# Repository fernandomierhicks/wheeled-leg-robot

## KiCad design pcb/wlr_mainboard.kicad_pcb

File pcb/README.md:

# Main board — Teensy 4.1 + ESP32 + CAN + JST-XH I/O

KiCad 10 project `wlr_mainboard` — replaces the hand-wired 90 × 70 mm perfboard
(`components/datasheets/custom board/`).

**Status (2026-10-08): schematic done (ERC 0 errors / 0 warnings), PCB fully
routed — DRC 0 violations, 0 unconnected, 0 schematic parity issues.**

> **Before ordering: double-check every pinout.** Connector pin orders were
> copied from the perfboard cables (photo, sketch and answers). The red note at
> the top of the schematic lists every connector and the specific doubts below.
> If a pin order changes, swap the nets in the schematic, update the PCB (F8)
> and re-route that connector.

## Files

| File | What |
|---|---|
| `wlr_mainboard.kicad_pro` | project; holds the OSH Park design rules and net classes |
| `wlr_mainboard.kicad_sch` | single A2 sheet; every pin goes to a net label or power symbol |
| `wlr_mainboard.kicad_pcb` | 4-layer board, routed, In1 GND / In2 +5V planes filled |
| `lib/wlr.kicad_sym` | Teensy 4.1, ESP32 DevKit V1 30-pin, SN65HVD230 module, power symbols `+3V3_TEENSY`, `+3V3_ESP32`, `VIN_TEENSY` |
| `lib/wlr.pretty/` | matching footprints (socket strips only in the courtyard, so parts can sit under the modules) |
| `sym-lib-table`, `fp-lib-table` | project-local libraries via `${KIPRJMOD}` |

These files are the source of truth: edit them in KiCad as usual and keep the
two in sync with *Tools → Update PCB from Schematic* (F8). They were generated
once by a throw-away script; nothing regenerates them.

## Board

- 90 × 70 mm, 4 × M2 (Ø2.2 NPTH) 2 mm in from the corners — same outline and
  holes as the perfboard (`cad/v5 Ai designed/Box/Electronics/CustomBoard`).
- Teensy USB and ESP32 USB-C at the top edge (they overhang it slightly).
- Teensy 4.1 and ESP32 on female sockets. Low parts sit under them:
  R1–R7, D1, D2, Q1 under the Teensy; U5, C2, R8–R12 under the ESP32. Seat
  them flat (keep under ~7 mm).
- CAN modules (U3 AK45 bus, U4 ODrive bus) stand on their 6-pin edge header,
  as on the perfboard; footprint assumes the module body on the +x side.
- Every JST-XH header has its latch side toward the board centre, like the
  perfboard, so the existing cables plug in the same way.
- Back silkscreen prints the pin name next to every connector pad.
- No copper pour or vias under the ESP32 antenna (rule area).
- Fully through-hole.

### OSH Park 4-layer

| Item | Value |
|---|---|
| Stackup | 1 oz / 7.87 mil prepreg / 0.5 oz / 39 mil core / 0.5 oz / 7.87 mil prepreg / 1 oz, FR408-HR (εr 3.61), ENIG, 1.6 mm nominal |
| Layers | L1 signal · L2 **GND plane** · L3 **+5V plane** · L4 signal |
| Rules (Board Setup) | 0.127 mm track / clearance, 0.254 mm drill, 0.102 mm annular ring, 0.381 mm copper-to-edge, 0.254 mm hole-to-copper |
| Net classes | Default 0.2 mm · Power 0.5 mm (`GND`, `+5V`, `VIN_TEENSY`, `+3V3_*`) · CAN 0.3 mm (`CAN?_H/L`) |
| Price | 90 × 70 mm ≈ 9.8 in² ≈ $98 for 3 boards ($10/in²) |

### Routing

Autorouted with Freerouting 2.5.0 (Specctra DSN → SES), then checked in KiCad.

- Signals on L1/L4 only; every GND and +5V pin connects straight to its plane
  through thermal reliefs (no GND/+5V traces).
- Widths: signals 0.2 mm, CAN pairs 0.3 mm, `+3V3_TEENSY` / `+3V3_ESP32` /
  `VIN_TEENSY` 0.5 mm. 17 vias (0.6 / 0.3 mm), ~2.6 m of track.
- No vias or pours in the ESP32 antenna area.
- To re-route with Freerouting: *File → Export → Specctra DSN*, shrink the DSN
  `boundary` ~0.25 mm (Freerouting ignores KiCad's 0.381 mm edge clearance),
  run with `--router.automatic_neckdown=false` (neckdown makes sub-0.127 mm
  traces), then *File → Import → Specctra Session*, refill zones (B), run DRC.
  Export the DSN from the board inside this folder, next to the `.kicad_pro`,
  or the net classes (power/CAN widths) are lost.

## Power

- `+5V` from J10 (buck output) feeds ESP32 VIN, the NeoPixel strip, IMU, ELRS
  receiver, buzzer and U5.
- Teensy VIN through **D1 (1N5817)**: Teensy USB can no longer back-feed the
  5 V rail, so the VUSB–VIN pad can stay uncut. The ESP32 DevKit still
  back-feeds `+5V` from its USB-C through its own diode (as on the perfboard).
- Two 3.3 V rails, never tied: `+3V3_TEENSY` (Teensy regulator) → CAN modules,
  UART6/7, I2C, spare header; `+3V3_ESP32` (DevKit regulator) → TFT, lasers,
  laser INT pull-ups, ESP32 spare header.

## Connectors

Orders are as seen on the board from the top (USB at the top). TX/RX are named
from the MCU (Teensy) side.

| Ref | Name | Footprint | Physical order on the board | Nets (pin 1 first) |
|---|---|---|---|---|
| J1 | BUZZER | XH 2p | top edge, left→right: BZ-, BZ+ | BUZZER_LOW, +5V |
| J2 | RGB_LED | XH 4p | left edge, top→bottom: B, G, GND, R | LED_R, GND, LED_G, LED_B |
| J3 | ELRS_RX | XH 4p | left edge, top→bottom: GND, 5V, RX (→Teensy 16), TX (Teensy 17→) | RC_TX, RC_RX_IN, +5V, GND |
| J4 | IMU_SIG | XH 6p | left edge, top→bottom: RST, INT, CS, AD0, SDA, SCL | IMU_SCK, IMU_MISO, IMU_MOSI, IMU_CS, IMU_INT, IMU_RST |
| J5 | IMU_PWR | XH 2p | left edge, top→bottom: GND, VCC (+5V) | +5V, GND |
| J6 | AK45_UART2 | XH 3p | bottom, inner row, left→right: GND, TX (Teensy 14), RX (Teensy 15) | AK2_RX, AK2_TX, GND |
| J7 | AK45_UART1 | XH 3p | bottom, outer row, left→right: GND, TX (Teensy 8), RX (Teensy 7) | AK1_RX, AK1_TX, GND |
| J8 | AK45_CAN | XH 2p | bottom, left→right: CANH, CANL | CAN2_L, CAN2_H |
| J9 | ODRIVE_CAN | XH 3p | bottom, left→right: GND, CANH, CANL | CAN3_L, CAN3_H, GND |
| J10 | 5V_IN | XH 2p | bottom, left→right: GND, +5V | +5V, GND |
| J11–J14 | LASER1–4 | XH 6p | bottom (1/2 outer row, 3/4 inner row), left→right: XSHUT, INT, SDA, SCL, GND, 3V3 | +3V3_ESP32, GND, TOF_SCL, TOF_SDA, LASERn_INT, LASERn_XSHUT |
| J15 | TFT_PWR | XH 2p | right edge, top→bottom: GND, 3V3 | GND, +3V3_ESP32 |
| J16 | TFT_SIG | XH 6p | right edge, top→bottom: SCL, SDA, RST, DC, CS, BL | TFT_SCK, TFT_MOSI, TFT_RST, TFT_DC, TFT_CS, TFT_BL |
| J17 | NEOPIXEL | XH 3p | right edge, top→bottom: 5V, GND, DATA | +5V, GND, NEO_DATA |
| J18 | LIMIT_L | XH 2p | *new*, right edge, top→bottom: GND, SIG (Teensy 23) | GND, LIMIT_L |
| J19 | LIMIT_R | XH 2p | *new*, right edge, top→bottom: GND, SIG (Teensy 22) | GND, LIMIT_R |
| J20 | UART6 | XH 4p | *new*, inner column, top→bottom: TX (24), RX (25), 3V3, GND | GND, +3V3_TEENSY, UART6_RX, UART6_TX |
| J21 | UART7 | XH 4p | *new*, inner column, top→bottom: RX (28), TX (29), 3V3, GND | GND, +3V3_TEENSY, UART7_TX, UART7_RX |
| J22 | I2C | XH 4p | *new*, inner column, top→bottom: SCL (19), SDA (18), 3V3, GND | GND, +3V3_TEENSY, I2C_SDA, I2C_SCL |
| J23 | TEENSY_GPIO | 1×14 header | *new*, top→bottom: 3V3, 26, 27, 32, GND, 41…33 — pins GND…33 sit level with the matching Teensy pins | — |
| J24 | ESP32_GPIO | 1×5 header | *new*, top→bottom: GND, 3V3, IO19, IO32, IO33 | — |

Lasers 1–4 = firmware sensors 0–3: XSHUT on ESP32 GPIO14/27/26/25, INT on
GPIO34/35/36/39 (10 kΩ pull-ups R9–R12; firmware still polls).

## Open checks before ordering

1. **IMU VCC = +5V** (as told): the BNO08x module must have its own 3.3 V regulator.
2. **IMU MOSI/MISO**: module `SDA` → Teensy 12 (MISO), `AD0` → Teensy 11 (MOSI),
   `SCL` → 13, per the BNO08x datasheet (H_SDA/H_MISO, SA0/H_MOSI).
   `firmware/robot_teensy/pinout.MD` lists SDA/AD0 the other way round —
   verify on the working perfboard.
3. **ELRS RX/TX** naming (J3) assumed from the Teensy side, like the AK45 UARTs.
4. **CAN termination**: the board is one end of each bus — check whether the
   HiLetgo module has a 120 Ω resistor fitted.
5. Confirm the CAN module stands with its body toward the Teensy (+x).
6. Not routed to the module: the IMU `PS0/WAKE` pin (`lib/IMU/README.md` asks
   for it on a future board, but the module only brings it out on solder
   bridges). A spare pin on J23 plus a flying wire would do.

## Parts

Through-hole only.

| Qty | Refs | Part |
|---|---|---|
| 1 | U1 | Teensy 4.1 + 2 × 1×24 female socket (2.54 mm) |
| 1 | U2 | ESP32 DevKit V1 30-pin USB-C + 2 × 1×15 female socket |
| 2 | U3, U4 | HiLetgo SN65HVD230 CAN board |
| 1 | U5 | 74AHCT125 (DIP-14, solder directly — no socket, it sits under the ESP32) |
| 1 | D1 | 1N5817 |
| 1 | D2 | 1N4148 |
| 1 | Q1 | 2N3904 (TO-92) |
| 3 | R1–R3 | 33 Ω (LED) |
| 2 | R4, R5 | 1 kΩ (buzzer base, ELRS RX series) |
| 2 | R6, R7 | 4.7 kΩ (I2C pull-ups) |
| 1 | R8 | 330 Ω (NeoPixel data) |
| 4 | R9–R12 | 10 kΩ (laser INT pull-ups) |
| 1 | C1 | 100 µF 10 V radial, Ø6.3 mm, 2.5 mm pitch |
| 1 | C2 | 100 nF disc, 5 mm pitch |
| 7 | J1, J5, J8, J10, J15, J18, J19 | JST B2B-XH-A |
| 4 | J6, J7, J9, J17 | JST B3B-XH-A |
| 5 | J2, J3, J20, J21, J22 | JST B4B-XH-A |
| 6 | J4, J11–J14, J16 | JST B6B-XH-A |
| 1 | J23 | 1×14 male header 2.54 mm |
| 1 | J24 | 1×5 male header 2.54 mm |

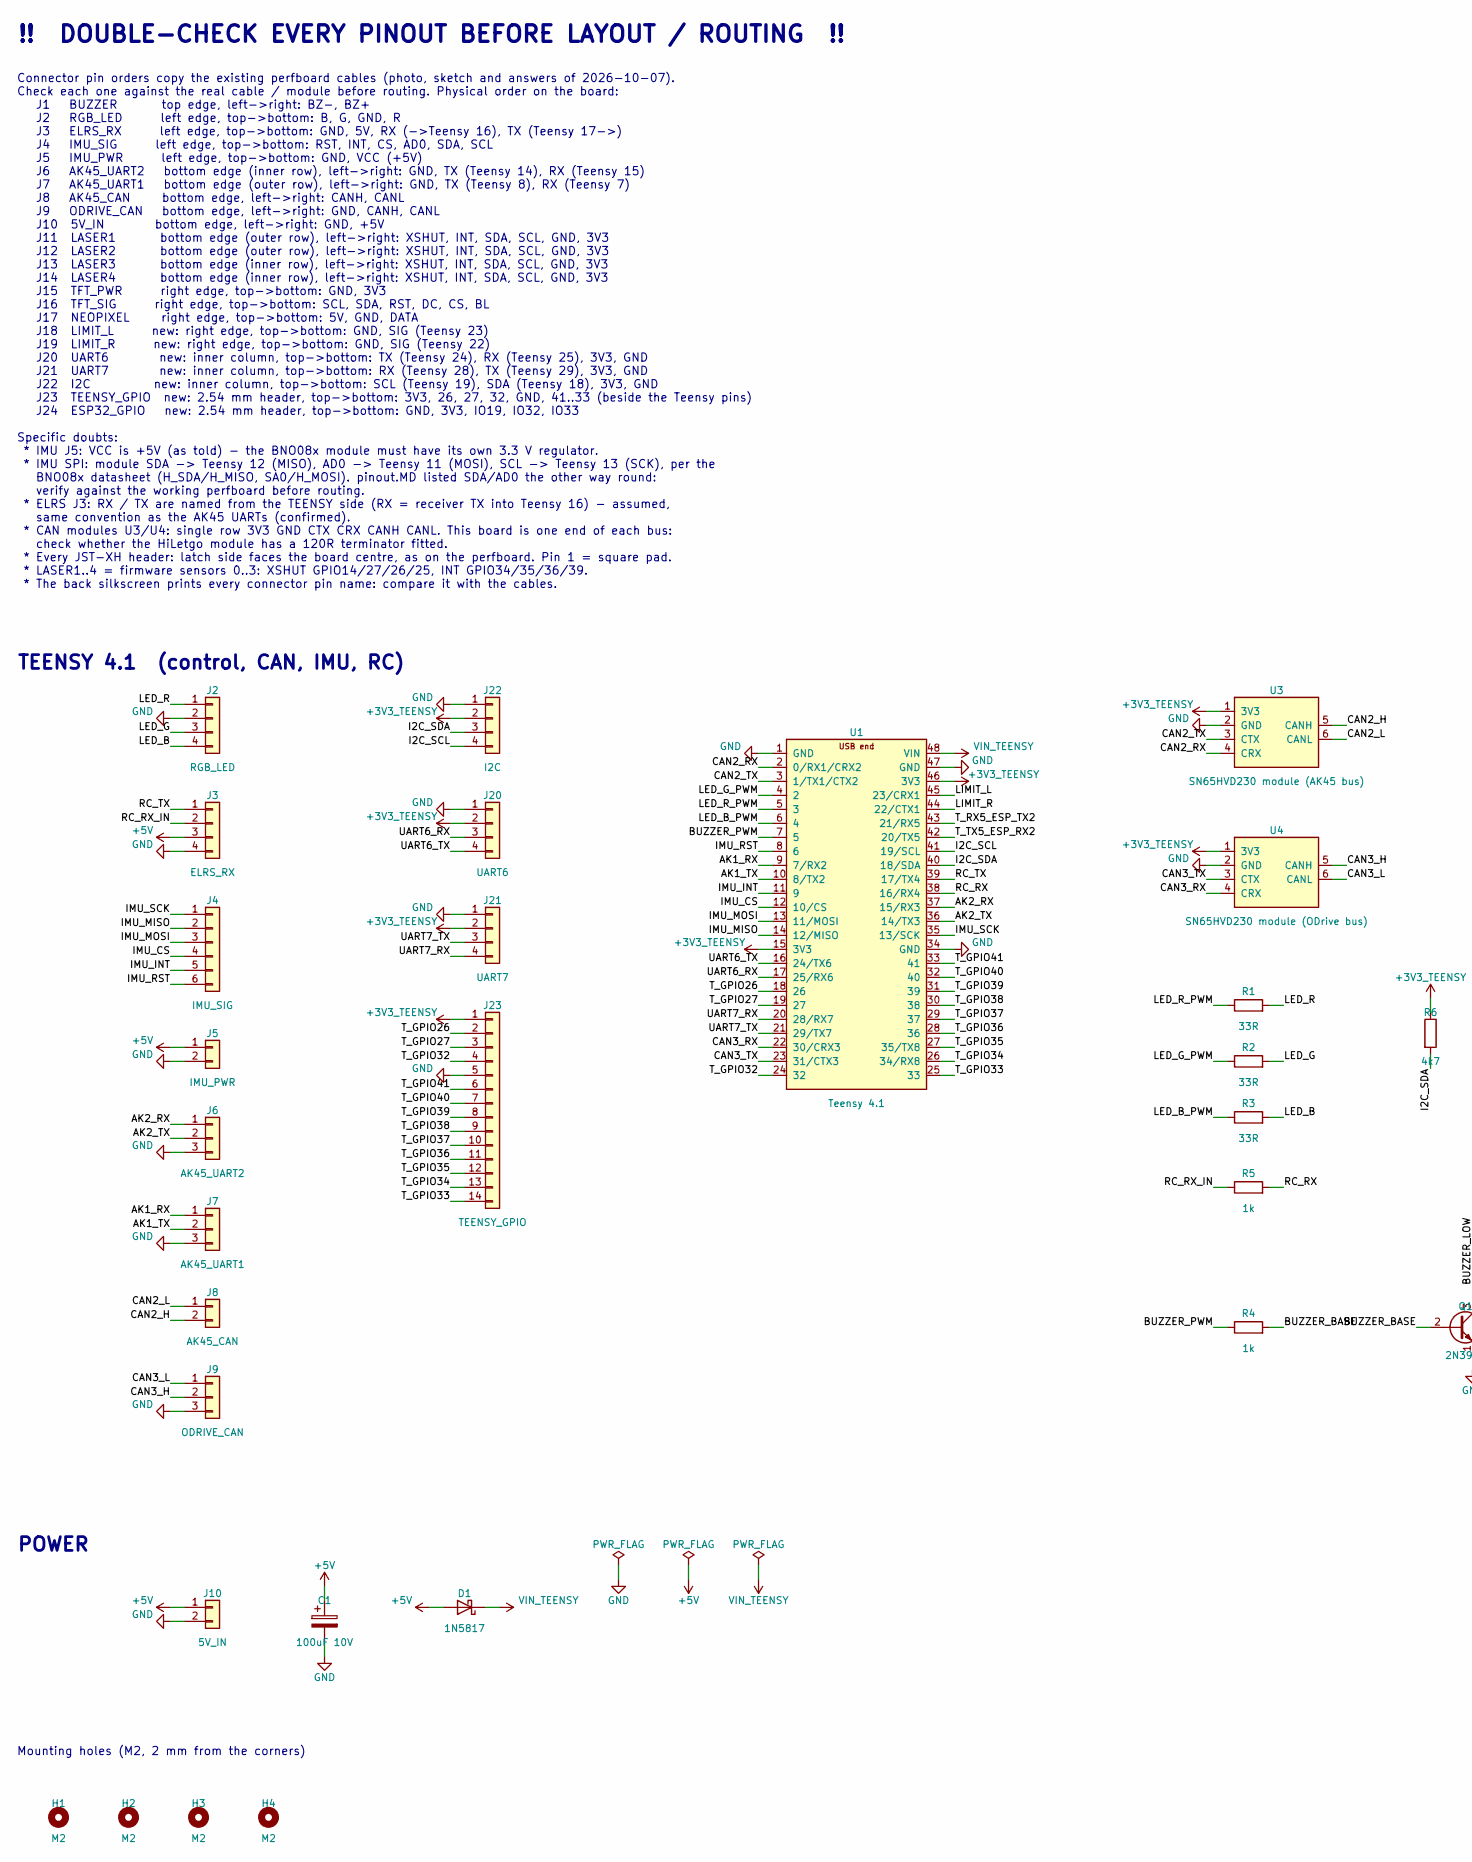
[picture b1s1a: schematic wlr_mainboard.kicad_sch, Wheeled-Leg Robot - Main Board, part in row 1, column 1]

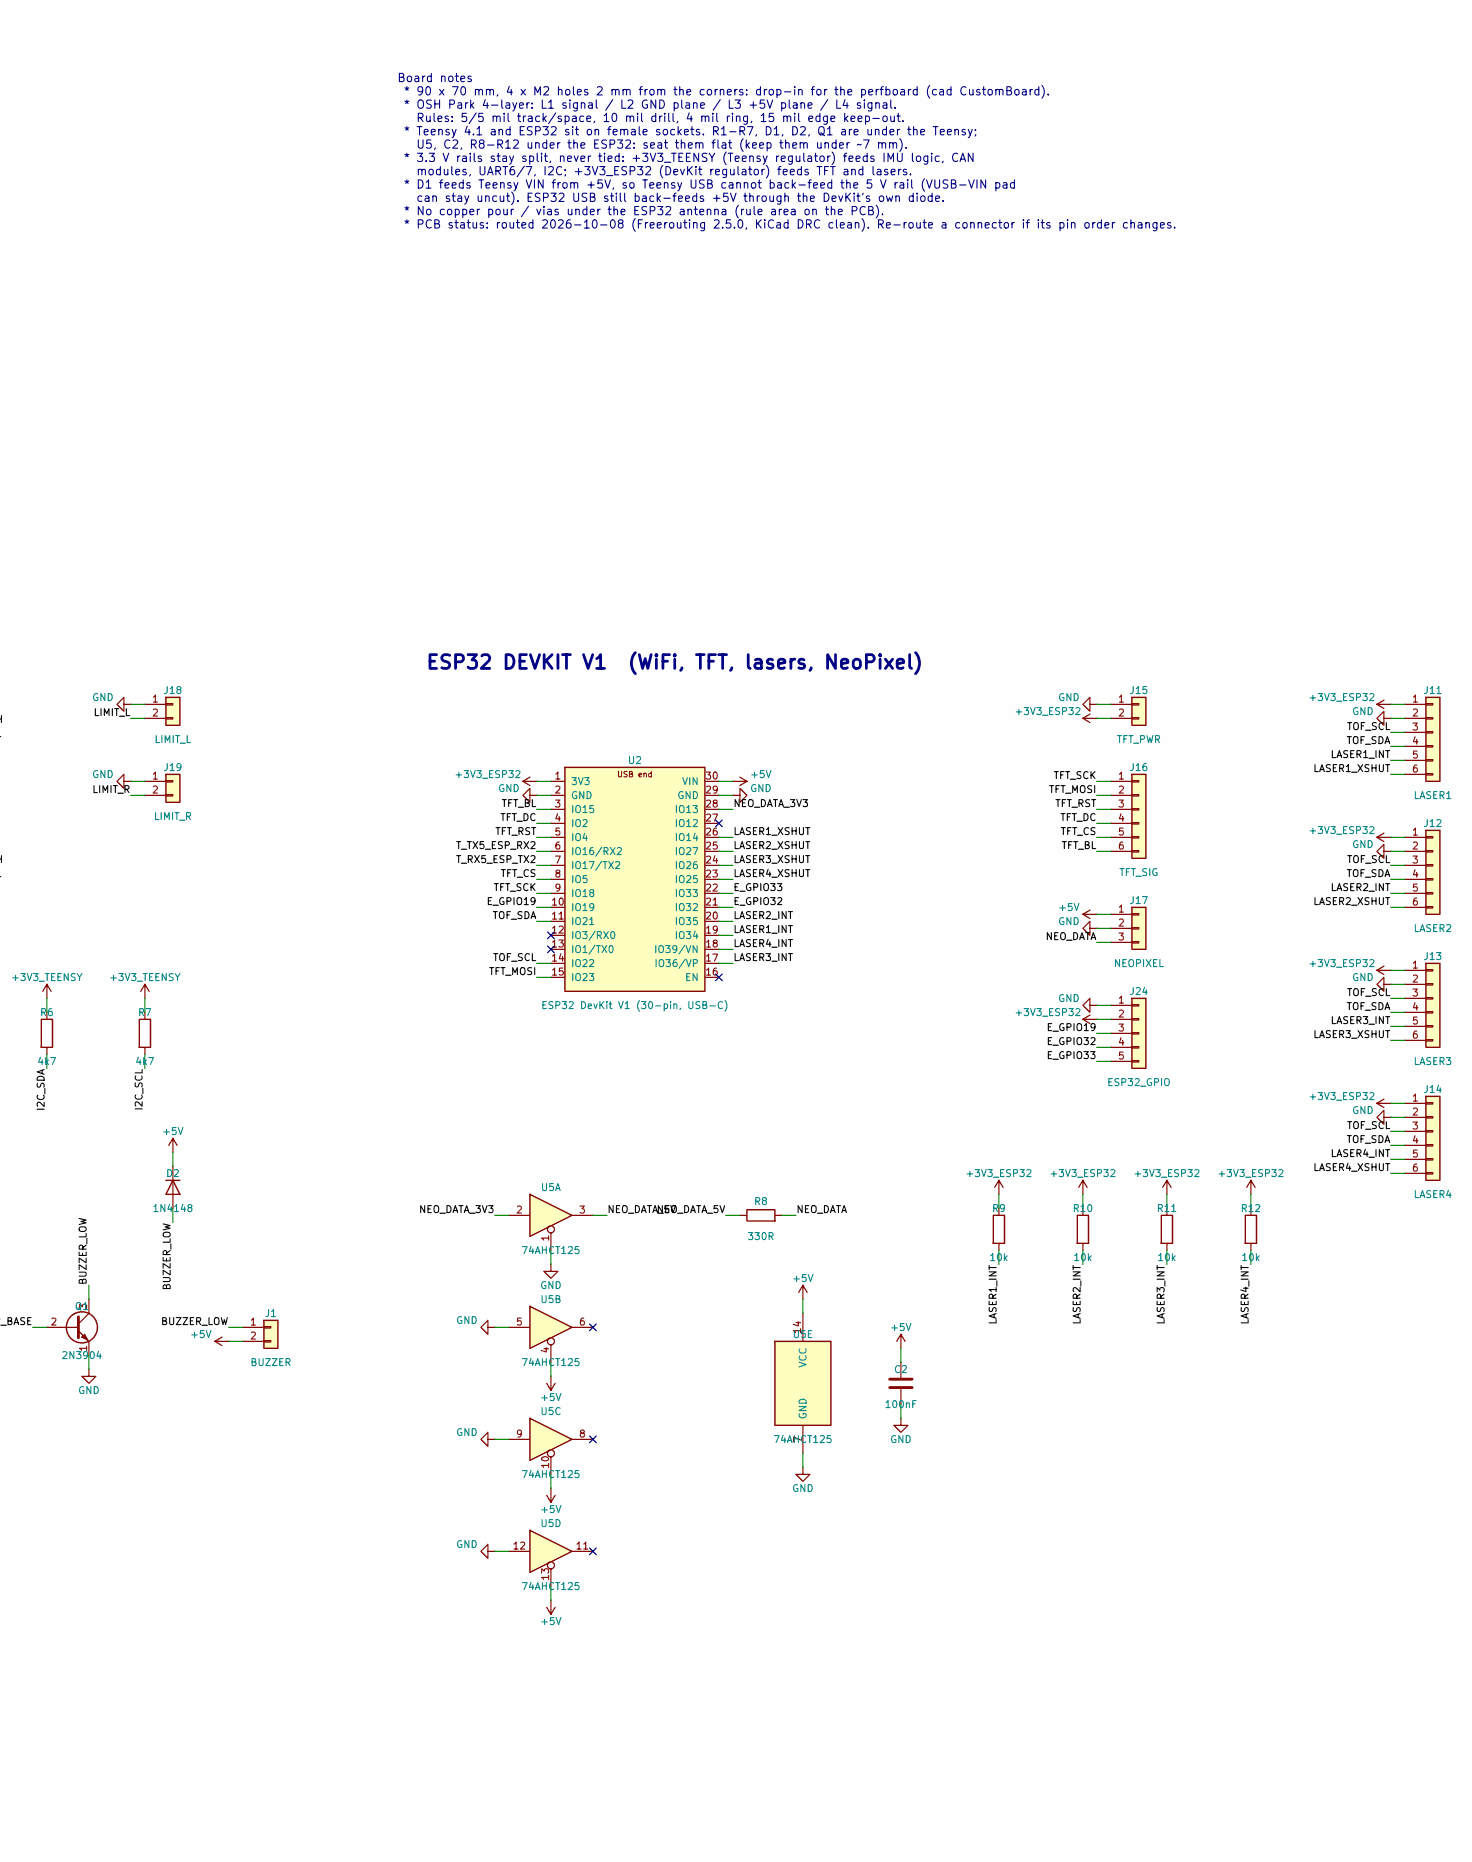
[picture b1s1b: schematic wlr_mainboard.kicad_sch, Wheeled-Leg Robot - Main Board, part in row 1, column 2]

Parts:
C1: 100uF 10V; CP_Radial_D6.3mm_P2.50mm
C2: 100nF; C_Disc_D5.0mm_W2.5mm_P5.00mm
D1: 1N5817; D_DO-41_SOD81_P7.62mm_Horizontal
D2: 1N4148; D_DO-35_SOD27_P7.62mm_Horizontal
H1, H2, H3, H4: M2; MountingHole_2.2mm_M2
J1: BUZZER; JST_XH_B2B-XH-A_1x02_P2.50mm_Vertical
J2: RGB_LED; JST_XH_B4B-XH-A_1x04_P2.50mm_Vertical
J3: ELRS_RX; JST_XH_B4B-XH-A_1x04_P2.50mm_Vertical
J4: IMU_SIG; JST_XH_B6B-XH-A_1x06_P2.50mm_Vertical
J5: IMU_PWR; JST_XH_B2B-XH-A_1x02_P2.50mm_Vertical
J6: AK45_UART2; JST_XH_B3B-XH-A_1x03_P2.50mm_Vertical
J7: AK45_UART1; JST_XH_B3B-XH-A_1x03_P2.50mm_Vertical
J8: AK45_CAN; JST_XH_B2B-XH-A_1x02_P2.50mm_Vertical
J9: ODRIVE_CAN; JST_XH_B3B-XH-A_1x03_P2.50mm_Vertical
J10: 5V_IN; JST_XH_B2B-XH-A_1x02_P2.50mm_Vertical
J11: LASER1; JST_XH_B6B-XH-A_1x06_P2.50mm_Vertical
J12: LASER2; JST_XH_B6B-XH-A_1x06_P2.50mm_Vertical
J13: LASER3; JST_XH_B6B-XH-A_1x06_P2.50mm_Vertical
J14: LASER4; JST_XH_B6B-XH-A_1x06_P2.50mm_Vertical
J15: TFT_PWR; JST_XH_B2B-XH-A_1x02_P2.50mm_Vertical
J16: TFT_SIG; JST_XH_B6B-XH-A_1x06_P2.50mm_Vertical
J17: NEOPIXEL; JST_XH_B3B-XH-A_1x03_P2.50mm_Vertical
J18: LIMIT_L; JST_XH_B2B-XH-A_1x02_P2.50mm_Vertical
J19: LIMIT_R; JST_XH_B2B-XH-A_1x02_P2.50mm_Vertical
J20: UART6; JST_XH_B4B-XH-A_1x04_P2.50mm_Vertical
J21: UART7; JST_XH_B4B-XH-A_1x04_P2.50mm_Vertical
J22: I2C; JST_XH_B4B-XH-A_1x04_P2.50mm_Vertical
J23: TEENSY_GPIO; PinHeader_1x14_P2.54mm_Vertical
J24: ESP32_GPIO; PinHeader_1x05_P2.54mm_Vertical
Q1: 2N3904; TO-92_Inline
R1, R2, R3: 33R; R_Axial_DIN0207_L6.3mm_D2.5mm_P7.62mm_Horizontal
R4, R5: 1k; R_Axial_DIN0207_L6.3mm_D2.5mm_P7.62mm_Horizontal
R6, R7: 4k7; R_Axial_DIN0207_L6.3mm_D2.5mm_P7.62mm_Horizontal
R8: 330R; R_Axial_DIN0207_L6.3mm_D2.5mm_P7.62mm_Horizontal
R9, R10, R11, R12: 10k; R_Axial_DIN0207_L6.3mm_D2.5mm_P7.62mm_Horizontal
U1: Teensy 4.1; Teensy_4.1_Socket
U2: ESP32 DevKit V1 (30-pin, USB-C); ESP32_DevKit_V1_30P_Socket
U3: SN65HVD230 module (AK45 bus); SN65HVD230_Module_Standing
U4: SN65HVD230 module (ODrive bus); SN65HVD230_Module_Standing
U5: 74AHCT125; DIP-14_W7.62mm

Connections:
+3V3_ESP32: J11.1, J12.1, J13.1, J14.1, J15.2, J24.2, R9.1, R10.1, R11.1, R12.1, U2.1 (3V3)
+3V3_TEENSY: J20.2, J21.2, J22.2, J23.1, R6.1, R7.1, U1.15 (3V3), U1.46 (3V3), U3.1 (3V3), U4.1 (3V3)
+5V: C1.1, C2.1, D1.2 (A), D2.1 (K), J1.2, J3.3, J5.1, J10.1, J17.1, U2.30 (VIN), U5.4, U5.10, U5.13, U5.14 (VCC)
/AK1_RX: J7.1, U1.9 (7/RX2)
/AK1_TX: J7.2, U1.10 (8/TX2)
/AK2_RX: J6.1, U1.37 (15/RX3)
/AK2_TX: J6.2, U1.36 (14/TX3)
/BUZZER_BASE: Q1.2 (B), R4.2
/BUZZER_LOW: D2.2 (A), J1.1, Q1.3 (C)
/BUZZER_PWM: R4.1, U1.7 (5)
/CAN2_H: J8.2, U3.5 (CANH)
/CAN2_L: J8.1, U3.6 (CANL)
/CAN2_RX: U1.2 (0/RX1/CRX2), U3.4 (CRX)
/CAN2_TX: U1.3 (1/TX1/CTX2), U3.3 (CTX)
/CAN3_H: J9.2, U4.5 (CANH)
/CAN3_L: J9.1, U4.6 (CANL)
/CAN3_RX: U1.22 (30/CRX3), U4.4 (CRX)
/CAN3_TX: U1.23 (31/CTX3), U4.3 (CTX)
/E_GPIO19: J24.3, U2.10 (IO19)
/E_GPIO32: J24.4, U2.21 (IO32)
/E_GPIO33: J24.5, U2.22 (IO33)
/I2C_SCL: J22.4, R7.2, U1.41 (19/SCL)
/I2C_SDA: J22.3, R6.2, U1.40 (18/SDA)
/IMU_CS: J4.4, U1.12 (10/CS)
/IMU_INT: J4.5, U1.11 (9)
/IMU_MISO: J4.2, U1.14 (12/MISO)
/IMU_MOSI: J4.3, U1.13 (11/MOSI)
/IMU_RST: J4.6, U1.8 (6)
/IMU_SCK: J4.1, U1.35 (13/SCK)
/LASER1_INT: J11.5, R9.2, U2.19 (IO34)
/LASER1_XSHUT: J11.6, U2.26 (IO14)
/LASER2_INT: J12.5, R10.2, U2.20 (IO35)
/LASER2_XSHUT: J12.6, U2.25 (IO27)
/LASER3_INT: J13.5, R11.2, U2.17 (IO36/VP)
/LASER3_XSHUT: J13.6, U2.24 (IO26)
/LASER4_INT: J14.5, R12.2, U2.18 (IO39/VN)
/LASER4_XSHUT: J14.6, U2.23 (IO25)
/LED_B: J2.4, R3.2
/LED_B_PWM: R3.1, U1.6 (4)
/LED_G: J2.3, R2.2
/LED_G_PWM: R2.1, U1.4 (2)
/LED_R: J2.1, R1.2
/LED_R_PWM: R1.1, U1.5 (3)
/LIMIT_L: J18.2, U1.45 (23/CRX1)
/LIMIT_R: J19.2, U1.44 (22/CTX1)
/NEO_DATA: J17.3, R8.2
/NEO_DATA_3V3: U2.28 (IO13), U5.2
/NEO_DATA_5V: R8.1, U5.3
/RC_RX: R5.2, U1.38 (16/RX4)
/RC_RX_IN: J3.2, R5.1
/RC_TX: J3.1, U1.39 (17/TX4)
/TFT_BL: J16.6, U2.3 (IO15)
/TFT_CS: J16.5, U2.8 (IO5)
/TFT_DC: J16.4, U2.4 (IO2)
/TFT_MOSI: J16.2, U2.15 (IO23)
/TFT_RST: J16.3, U2.5 (IO4)
/TFT_SCK: J16.1, U2.9 (IO18)
/TOF_SCL: J11.3, J12.3, J13.3, J14.3, U2.14 (IO22)
/TOF_SDA: J11.4, J12.4, J13.4, J14.4, U2.11 (IO21)
/T_GPIO26: J23.2, U1.18 (26)
/T_GPIO27: J23.3, U1.19 (27)
/T_GPIO32: J23.4, U1.24 (32)
/T_GPIO33: J23.14, U1.25 (33)
/T_GPIO34: J23.13, U1.26 (34/RX8)
/T_GPIO35: J23.12, U1.27 (35/TX8)
/T_GPIO36: J23.11, U1.28 (36)
/T_GPIO37: J23.10, U1.29 (37)
/T_GPIO38: J23.9, U1.30 (38)
/T_GPIO39: J23.8, U1.31 (39)
/T_GPIO40: J23.7, U1.32 (40)
/T_GPIO41: J23.6, U1.33 (41)
/T_RX5_ESP_TX2: U1.43 (21/RX5), U2.7 (IO17/TX2)
/T_TX5_ESP_RX2: U1.42 (20/TX5), U2.6 (IO16/RX2)
/UART6_RX: J20.3, U1.17 (25/RX6)
/UART6_TX: J20.4, U1.16 (24/TX6)
/UART7_RX: J21.4, U1.20 (28/RX7)
/UART7_TX: J21.3, U1.21 (29/TX7)
GND: C1.2, C2.2, J2.2, J3.4, J5.2, J6.3, J7.3, J9.3, J10.2, J11.2, J12.2, J13.2, J14.2, J15.1, J17.2, J18.1, J19.1, J20.1, J21.1, J22.1, J23.5, J24.1, Q1.1 (E), U1.1 (GND), U1.34 (GND), U1.47 (GND), U2.2 (GND), U2.29 (GND), U3.2 (GND), U4.2 (GND), U5.1, U5.5, U5.7 (GND), U5.9, U5.12
VIN_TEENSY: D1.1 (K), U1.48 (VIN)

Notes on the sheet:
!! DOUBLE-CHECK EVERY PINOUT BEFORE LAYOUT / ROUTING !!
Board notes * 90 x 70 mm, 4 x M2 holes 2 mm from the corners: drop-in for the perfboard (cad CustomBoard). * OSH Park 4-layer: L1 signal / L2 GND plane / L3 +5V plane / L4 signal. Rules: 5/5 mil track/space, 10 mil drill, 4 mil ring, 15 mil edge keep-out. * Teensy 4.1 and ESP32 sit on female socket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
ESP32 DEVKIT V1 (WiFi, TFT, lasers, NeoPixel)
Mounting holes (M2, 2 mm from the corners)
POWER
TEENSY 4.1 (control, CAN, IMU, RC)
Connector pin orders copy the existing perfboard cables (photo, sketch and answers of 2026-10-07). Check each one against the real cable / module before routing. Physical order on the board: J1 BUZZER top edge, left->right: BZ-, BZ+ J2 RGB_LED left edge, top->bottom: B, G, GND, R J3 ELRS_RX left ed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

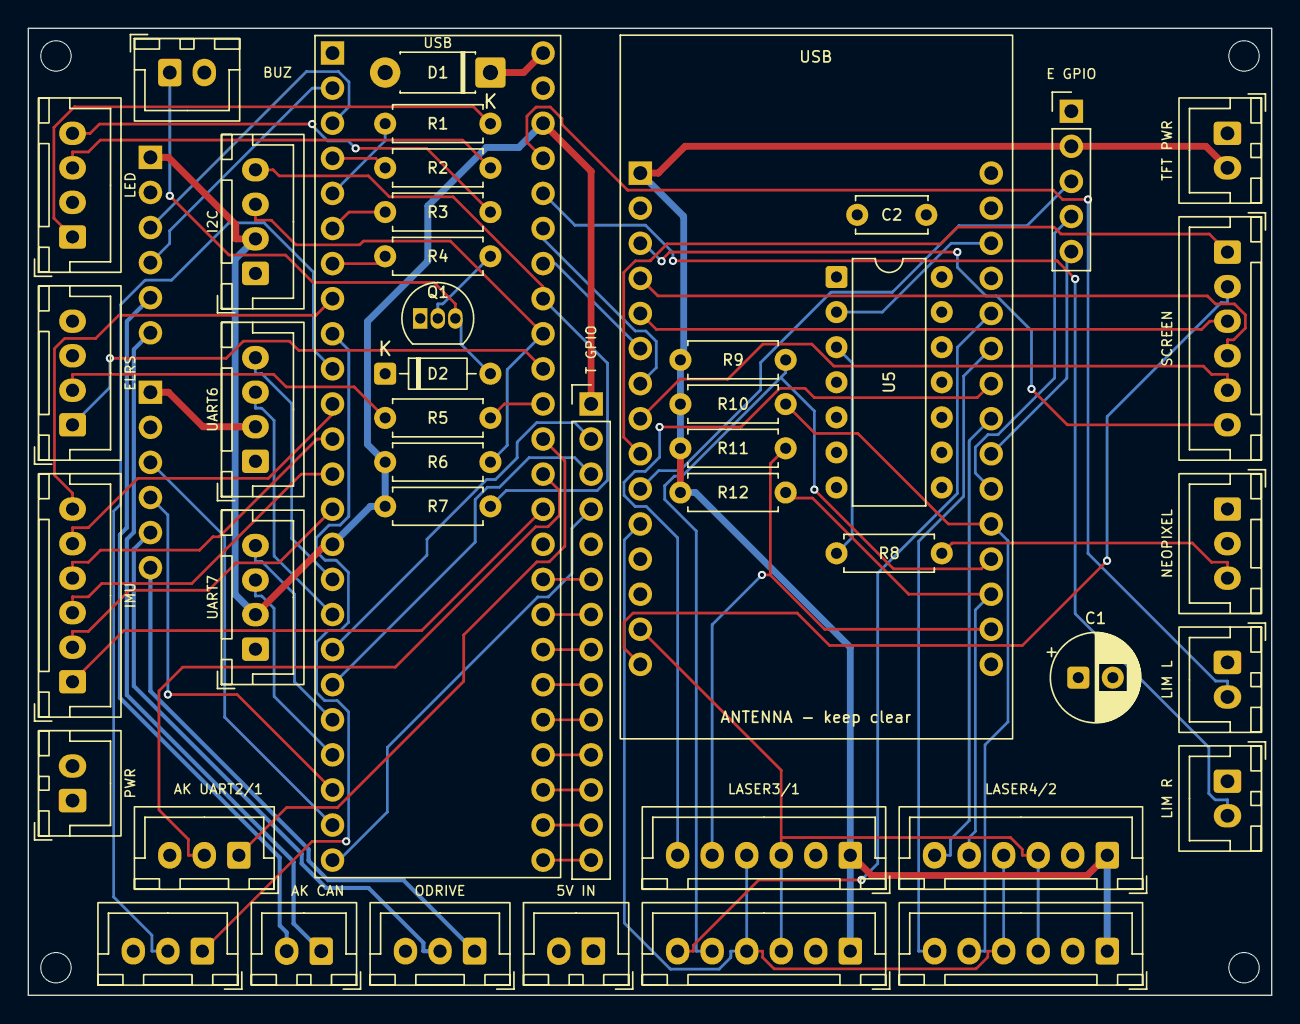
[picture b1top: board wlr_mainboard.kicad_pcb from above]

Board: 4 copper layers, 90.0 x 70.0 mm, 50 parts (0 on the bottom side), 79 nets.

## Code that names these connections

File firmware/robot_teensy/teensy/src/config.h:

#pragma once

// --- CAN buses ---
#define PIN_CAN2_TX      1  // AK45 hip motors (Serial1 unavailable on these pins)
#define PIN_CAN2_RX      0
#define PIN_CAN3_TX     31  // ODrive wheel motors
#define PIN_CAN3_RX     30

// --- IMU (BNO086, SPI0) ---
#define PIN_IMU_CS      10
#define PIN_IMU_INT      9
#define PIN_IMU_RST      6

// --- RGB LED ---
#define PIN_LED_R        3
#define PIN_LED_G        2
#define PIN_LED_B        4

// --- Passive buzzer (PWM tone) ---
#define PIN_BUZZER       5

// --- AK45 UART (Serial2 / Serial3, standard 2-wire TX/RX) ---
#define PIN_AK45_1_RX    7
#define PIN_AK45_1_TX    8
#define PIN_AK45_2_TX   14
#define PIN_AK45_2_RX   15
#define AK45_UART_BAUD   921600UL

// --- RC receiver (FlySky iBUS, Serial4 RX only) ---
#define PIN_IBUS_RX     16

// --- ESP32 link (Serial5) ---
#define PIN_ESP32_TX    20
#define PIN_ESP32_RX    21

// --- Hip/leg NC limit switches to GND (LOW=released, HIGH=pressed) ---
#define PIN_LIMIT_LEFT  23  // leg 1 / motor 1 / channel 1
#define PIN_LIMIT_RIGHT 22

// --- ESP32 UART baud ---
#define ESP32_BAUD      4000000UL

// --- Control loop ---
#define CONTROL_HZ      500

// --- AK45-10 hip motor CAN IDs (MIT Cheetah protocol, CAN1) ---
#define AK45_ID_L           11          // left hip motor
#define AK45_ID_R           12          // right hip motor

// --- ODrive wheel motor CAN ---
#define ODESC_NODE_L        0           // ODrive axis 0 — left wheel
#define ODESC_NODE_R        1           // ODrive axis 1 — right wheel
#define CAN_BAUD            1000000UL   // 1 Mbps
#define HIP_CAN_TIMEOUT_MS  50          // AK45 MIT feedback watchdog (looser than wheel encoders)
#define CAN_INTER_FRAME_US  100         // gap between back-to-back TX frames — under
                                          // re-characterization, was 500; a standard 8-byte
                                          // CAN frame at 1 Mbps takes ~110-130us worst-case
                                          // (bit-stuffed), so 500 was ~4x that

// --- Hip retract-switch calibration ---
// Motor/wiring orientation is a hardware property, not a runtime parameter.
// Signs use the normalized firmware frame after the left motor's mirroring.
#define CALIB_L_SEEK_DIR  (+1.0f)
#define CALIB_R_SEEK_DIR  (+1.0f)
// Tunable motion, current, range, timeout, and ramp settings are in
// ParamRegistry (generated from protocol/schema.json).

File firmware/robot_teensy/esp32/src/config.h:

#pragma once

// --- Teensy link (UART2: RX=GPIO16←Teensy pin20, TX=GPIO17→Teensy pin21) ---
#define TEENSY_UART_BAUD  4000000UL
#define TEENSY_UART_RX    16
#define TEENSY_UART_TX    17
#define UPLINK_QUEUE_LEN        24      // uplink_task queue depth — ~200 ms absorb at 100 frames/s
#define CONTROL_UPLINK_QUEUE_LEN 8      // command results/params/log messages, drained first
#define LOG_UPLINK_QUEUE_LEN     4      // ACK flow control keeps at most one data chunk in flight
#define UART_PARSE_BUDGET_BYTES  2048   // maximum Serial2 bytes parsed per loop pass
#define HOST_PARSE_BUDGET_BYTES   512   // maximum USB/TCP bytes parsed per loop pass
#define TEENSY_LINK_TIMEOUT_MS  1500    // single truth for "Teensy link up": TFT active-state,
                                         // Neopixel linked-state, and face-mode connected-state

// --- 2.0" TFT display (GMT020-02-9P, ST7789, SPI) ---
// VSPI bus: SCK=18, MOSI=23 (hardware defaults, shared)
#define TFT_CS   5
#define TFT_DC   2
#define TFT_RST  4
#define TFT_BLK  15   // backlight; tie to 3.3 V if GPIO control not needed

// --- WiFi telemetry ---
#ifndef WIFI_ENABLED
#define WIFI_ENABLED      1     // set to 0 to disable UDP broadcast + TCP server. Unlike the other
                                 // WiFi campaign toggles below, this wasn't previously overridable via
                                 // PLATFORMIO_BUILD_FLAGS — added the guard so a WiFi-free diagnostic
                                 // build (e.g. -D WIFI_ENABLED=0) is possible without editing this file.
#endif
#define TELEM_UDP_PORT    5005
#define CMD_TCP_PORT      5006
#define DISCOVERY_UDP_PORT 5007
#define WIFI_SESSION_LEASE_MS 3500

// --- ToF laser distance sensors (VL53L1X x4) ---
#define LASERS_ENABLED    0     // set to 1 once VL53L1X sensors are wired up

// --- Display personality ---
// 0 = PERS_ENGINEERING (telemetry panels), 1 = PERS_FACE (cartoon eyes),
// 2 = PERS_GLACIER (visor eyes + trace mouth, glacier_face.cpp)
// Change this to switch the power-on default; later the Teensy can override live.
// Overridable via PLATFORMIO_BUILD_FLAGS (-D DEFAULT_DISPLAY_PERSONALITY=2) like the WiFi toggles.
#ifndef DEFAULT_DISPLAY_PERSONALITY
#define DEFAULT_DISPLAY_PERSONALITY  2
#endif

// --- WiFi telemetry campaign build-time toggles ---
// All overridable via PLATFORMIO_BUILD_FLAGS (-D...) without editing this file,
// so test variants can be flashed without dirtying the tree.
#ifndef WIFI_TELEM_MODE
#define WIFI_TELEM_MODE      1   // 0=broadcast, 1=unicast to WIFI_UNICAST_IP (default —
                                 //   campaign result 2026-07-18: unicast eliminates the
                                 //   DTIM-clumping that made broadcast telemetry choppy)
#endif
#ifndef WIFI_UNICAST_IP
#define WIFI_UNICAST_IP      ""  // baked in by flash_monitor.py at flash time (auto-detected
                                 //   PC LAN IP); falls back to broadcast-like failure if unset —
                                 //   set explicitly via PLATFORMIO_BUILD_FLAGS if flashing outside the GUI
#endif
#ifndef WIFI_TELEM_COMBINED
#define WIFI_TELEM_COMBINED  1   // 1=single atomic TelemetryPayload datagram (production default)
#endif
#ifndef WIFI_TX_POWER_MAX
#define WIFI_TX_POWER_MAX    0   // 0=default, 1=WiFi.setTxPower(max) in setup()
#endif
#ifndef NEO_ENABLED
#define NEO_ENABLED          1   // 0=skip starting neo_task (FastLED isolation test)
#endif
#ifndef DISPLAY_ENABLED
#define DISPLAY_ENABLED      1   // 0=skip starting display_task (core-0 contention isolation —
                                 //   the display is the heaviest core-0 load)
#endif
#ifndef WIFI_DIAG_HZ
#define WIFI_DIAG_HZ         5   // bumped 2->5 (Phase 3, UARTplat.md): snappier GUI ESP32-alive detection
#endif
#ifndef ESP32_STATUS_HZ
#define ESP32_STATUS_HZ      5   // ESP32->Teensy link heartbeat rate (Phase 3, UARTplat.md)
#endif
#ifndef WIFI_TRANSPORT_GATING
#define WIFI_TRANSPORT_GATING 0  // 0=always send WiFi telemetry when connected (current), 1=honor
                                 //   CMD_ID_SET_TELEM_TRANSPORT and suppress WiFi telemetry sends
                                 //   when the GUI has announced it's reading USB instead
#endif

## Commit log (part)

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2026-06-10 Add ESTOP reset/MCU reboot, hip MIT setpoint caching, and GUI command path refactor
    - Teensy: CMD_ID_REBOOT triggers full MCU reset; ESTOP can now transition back
    to STARTUP via a reset request, clearing the fault code
    - Hip motors: cache MIT setpoints and re-send them every poll tick, falling
    back to the safe zero-torque ping on ESTOP or stale commands
    - LED: add flash_then_pulse for a reset-accepted indicator; boot rainbow/chime
    sequence on startup
2026-06-15 Add hardstop calibration state machine and ESTOP request path
    Introduces a STATE_CALIBRATION state (lib/Calibration) that seeks hip
    hardstops, computes joint limits, and homes before returning to
    STANDBY, plus a stateMachine_request_estop() path reachable from any
    non-ESTOP state. GUI/comm protocol and hip motor handling updated to
    support the new calibration flow; HANDOFF.md/frames.md/TODO.txt
    document the follow-up work for surfacing calibration events in the GUI.
